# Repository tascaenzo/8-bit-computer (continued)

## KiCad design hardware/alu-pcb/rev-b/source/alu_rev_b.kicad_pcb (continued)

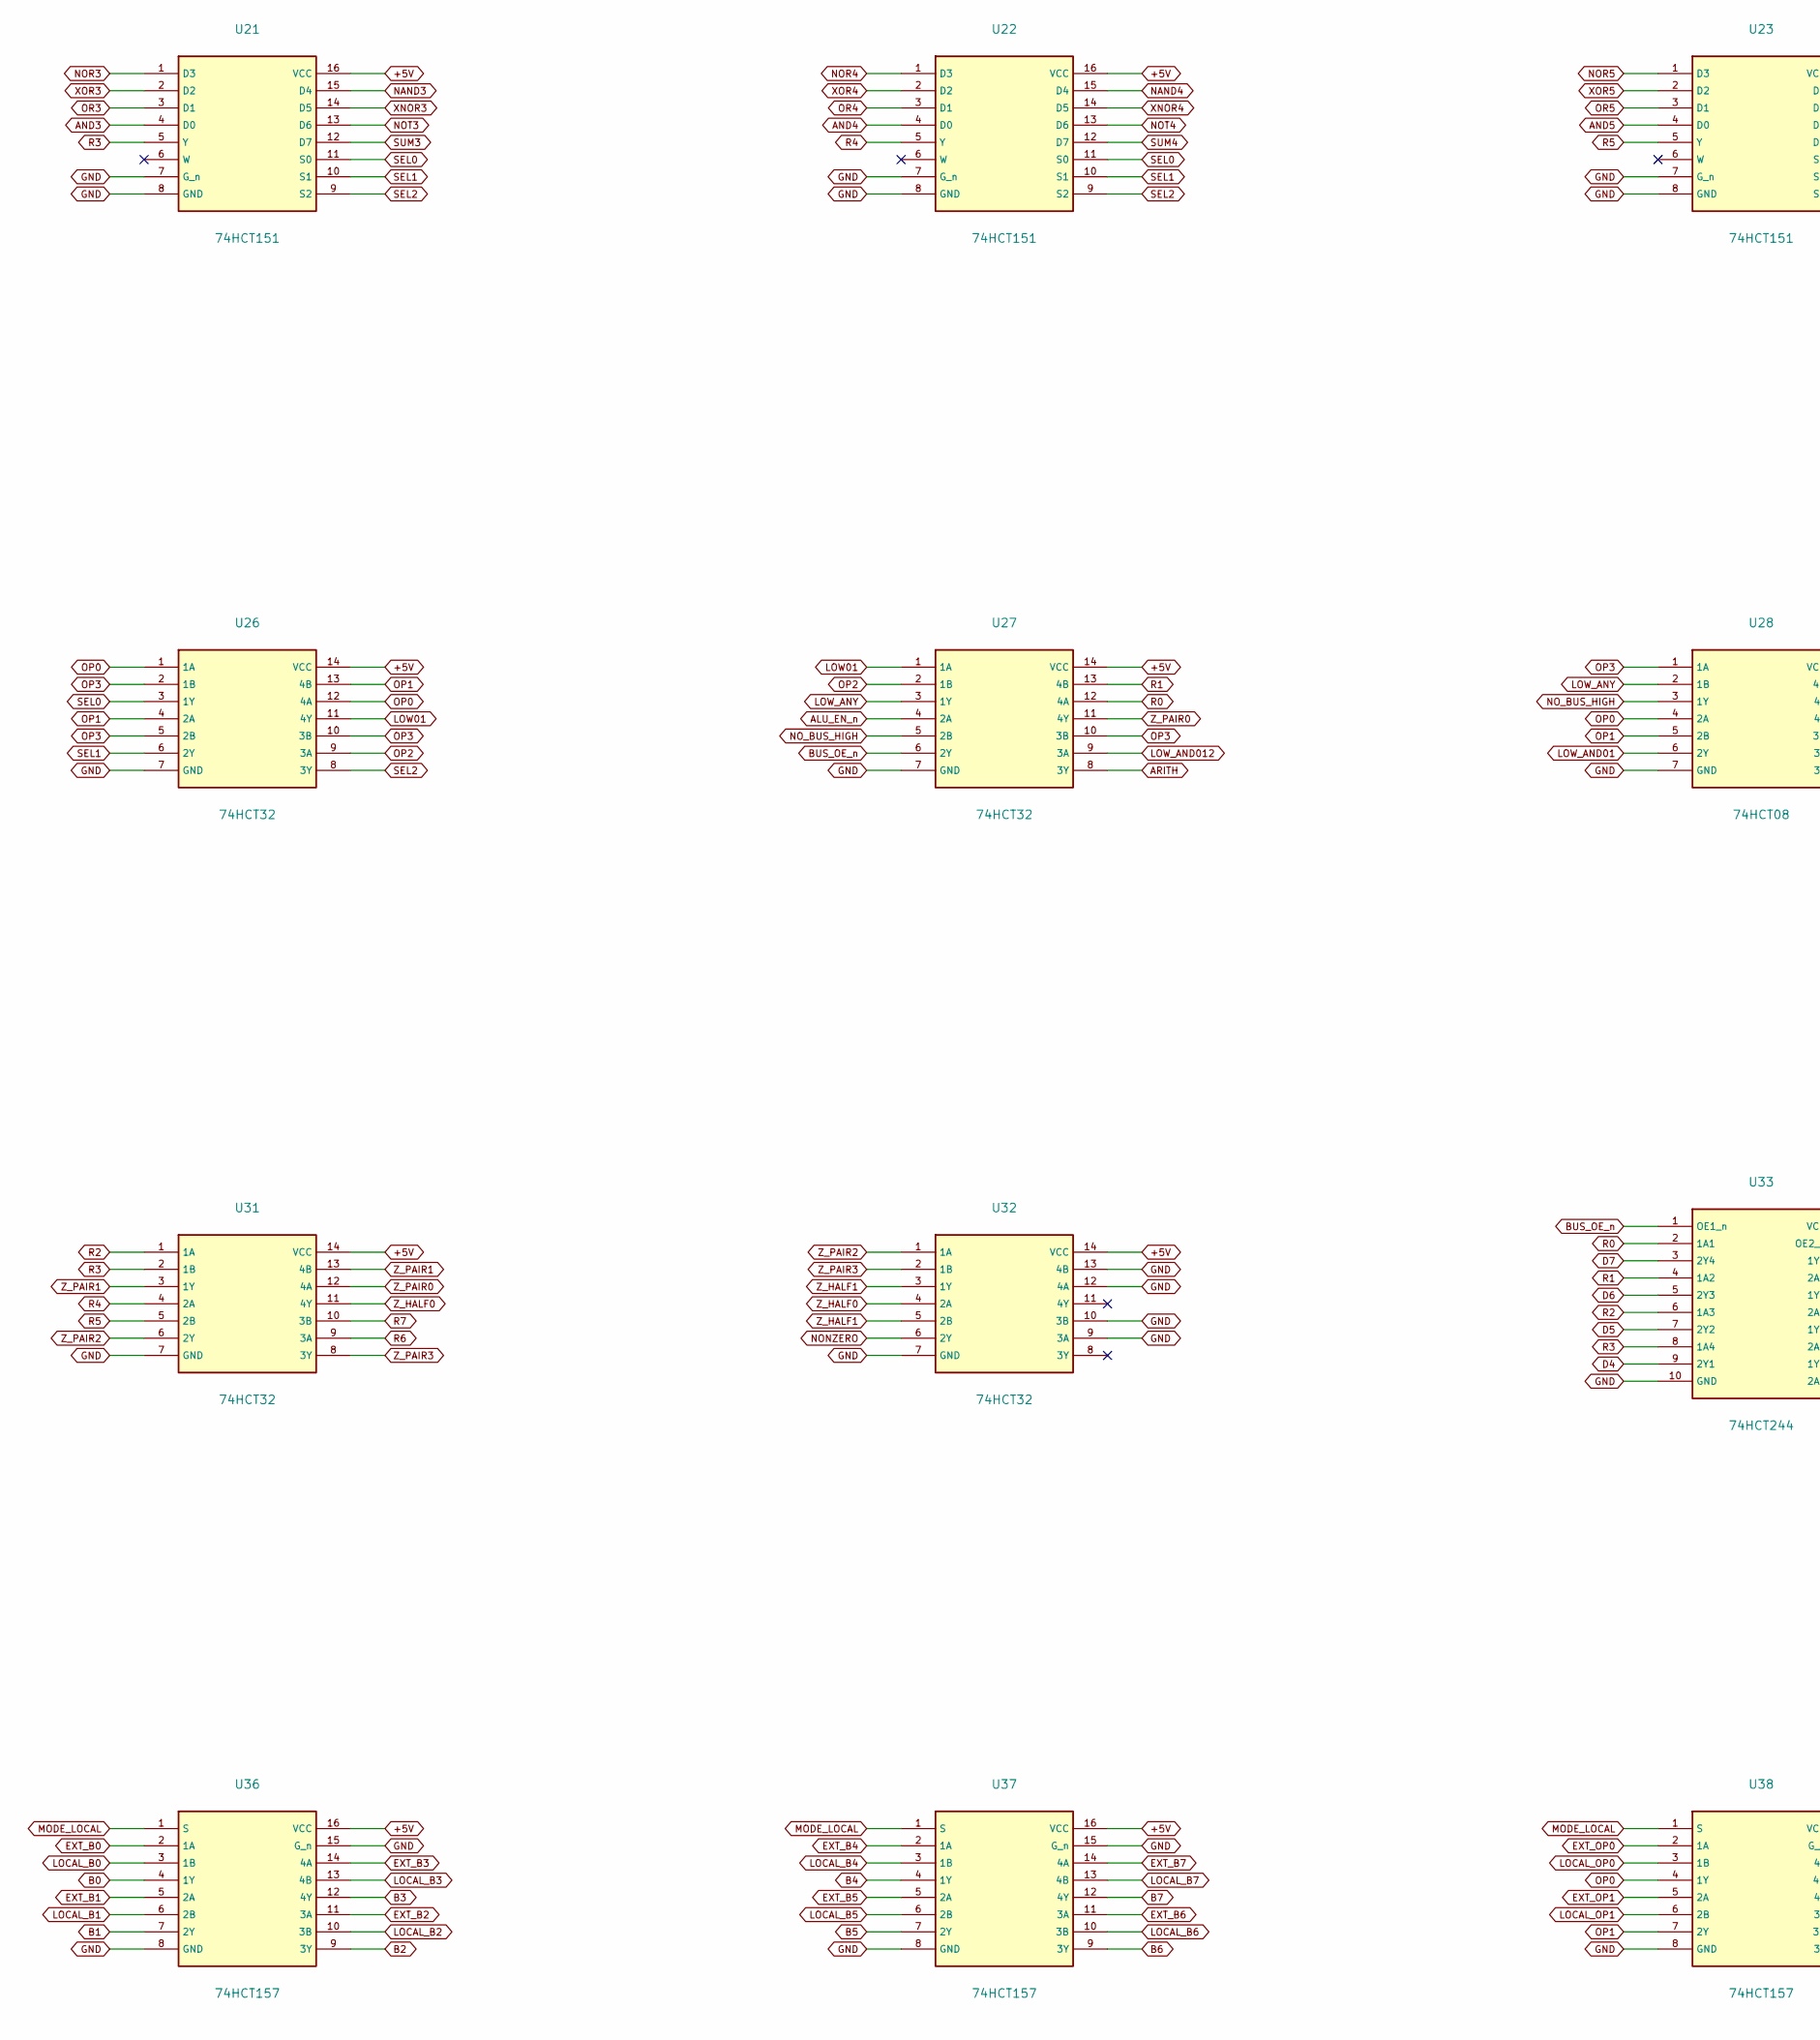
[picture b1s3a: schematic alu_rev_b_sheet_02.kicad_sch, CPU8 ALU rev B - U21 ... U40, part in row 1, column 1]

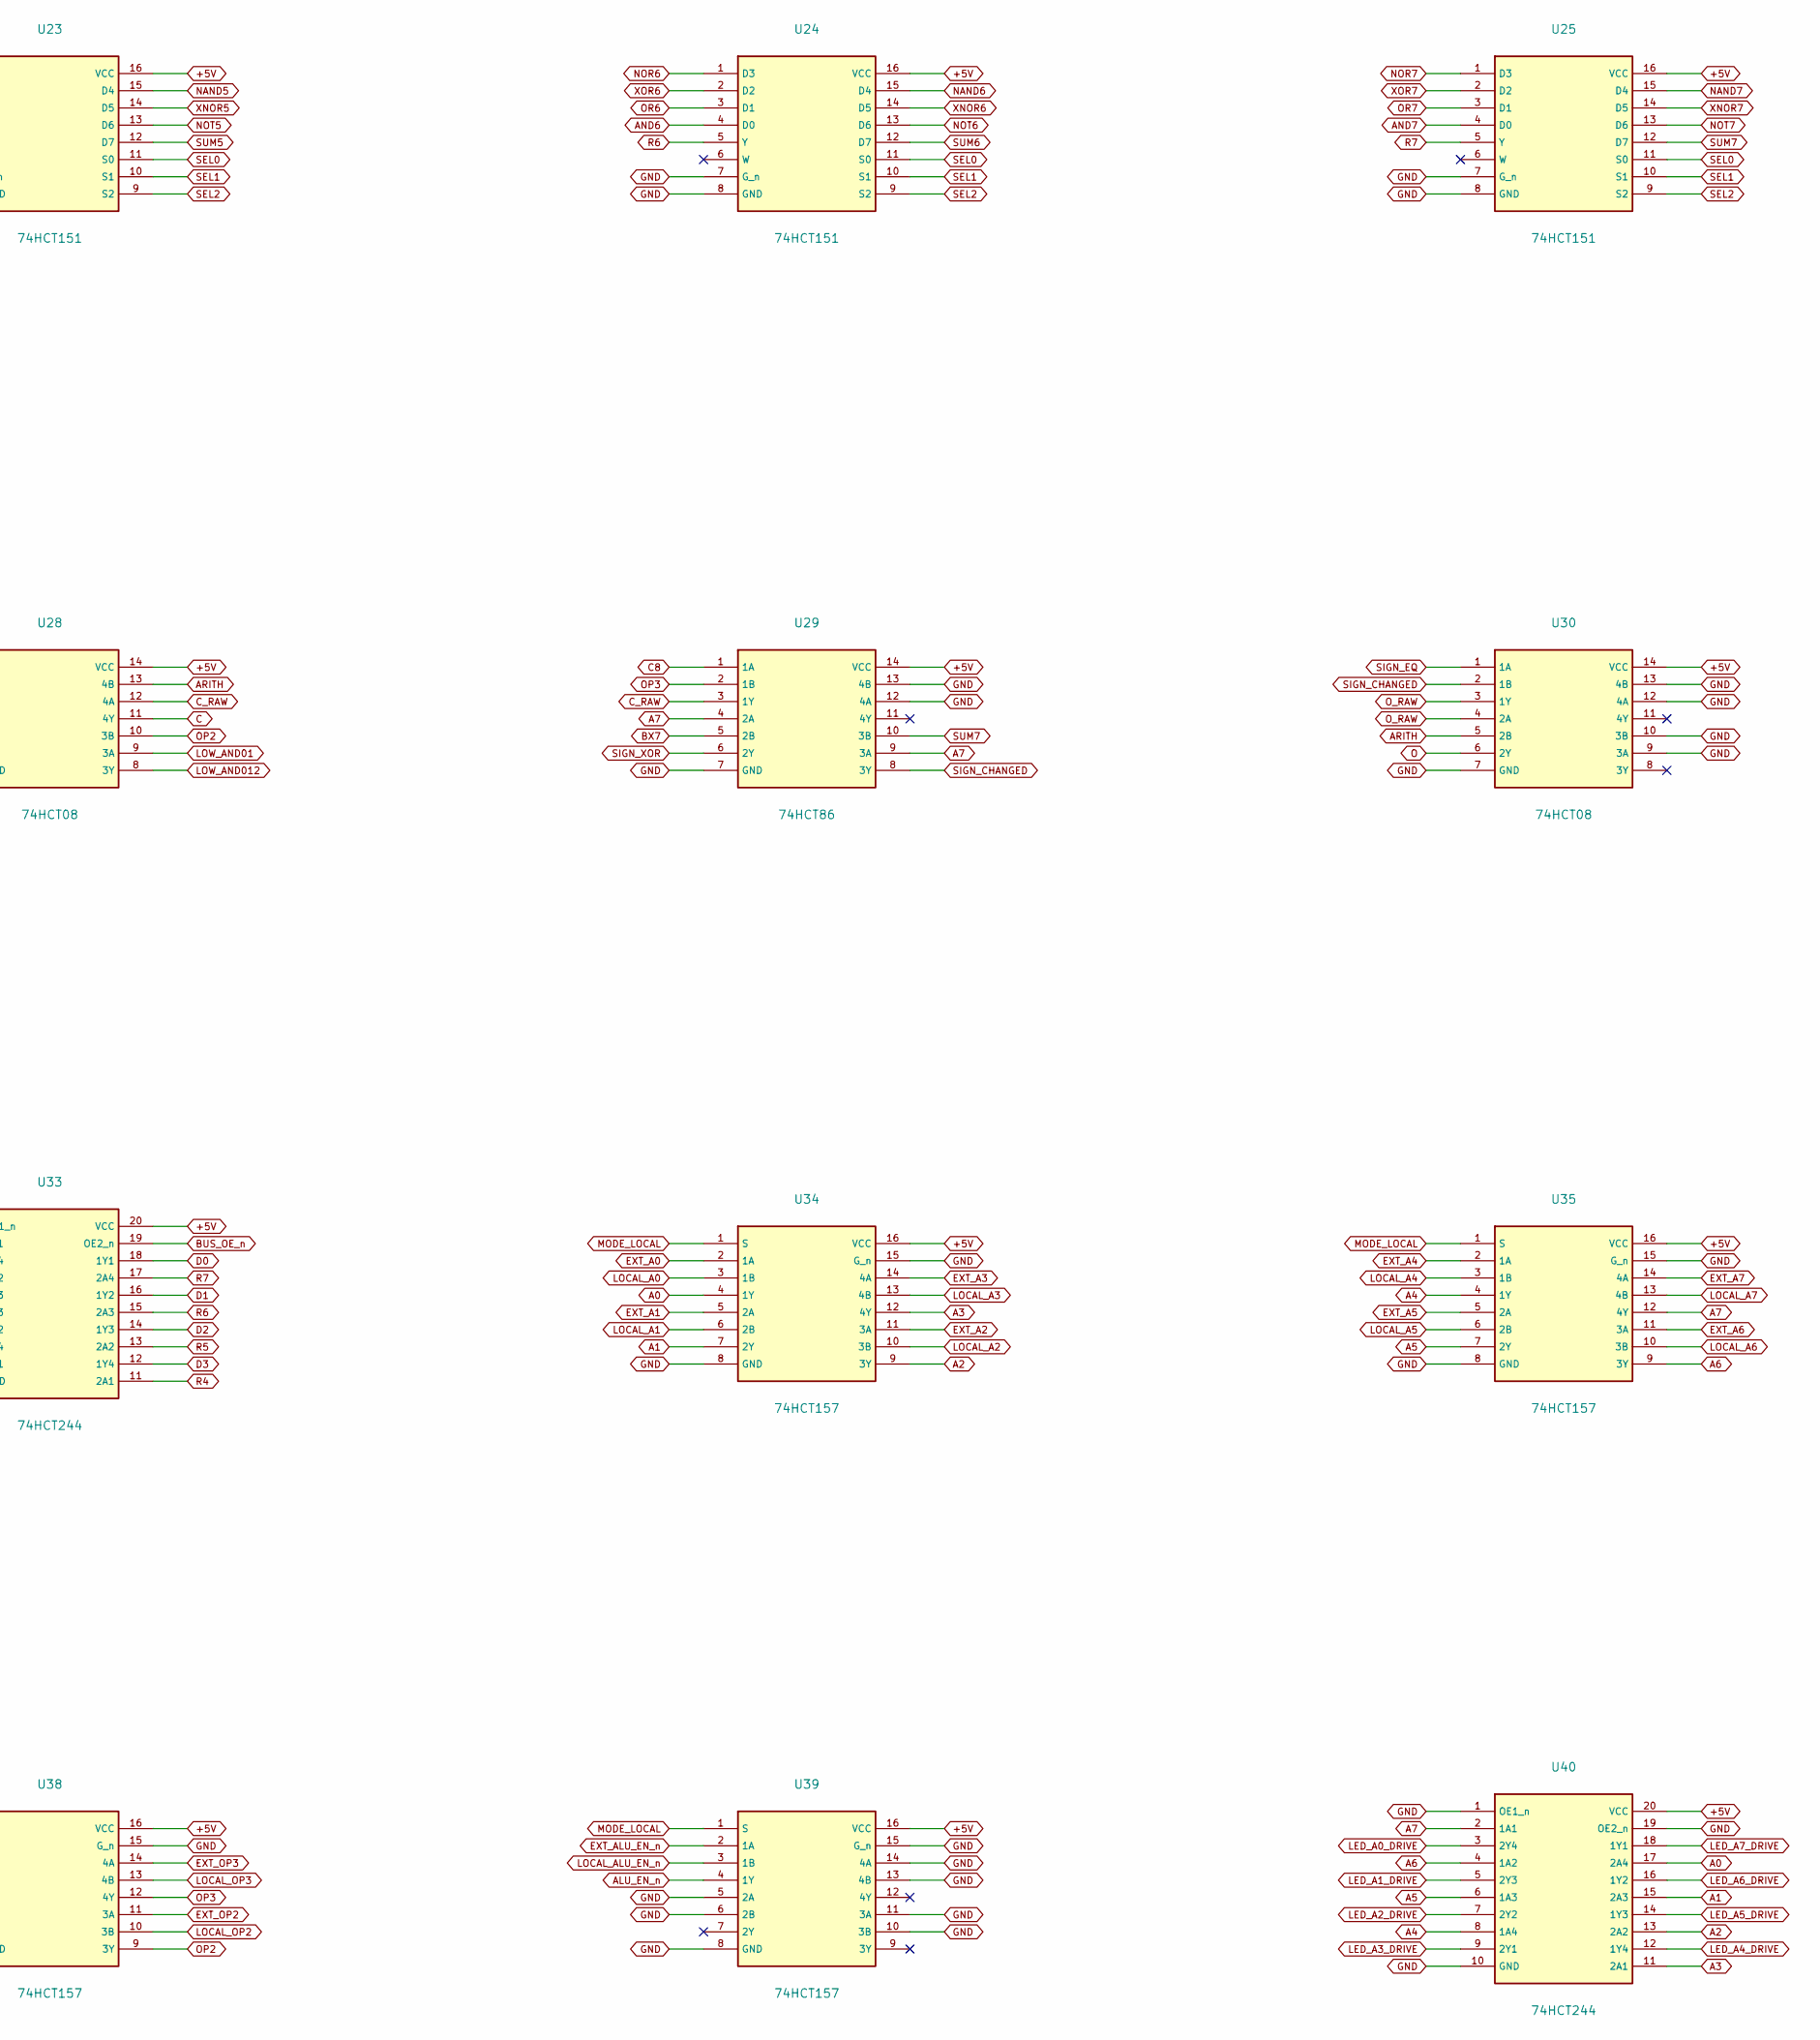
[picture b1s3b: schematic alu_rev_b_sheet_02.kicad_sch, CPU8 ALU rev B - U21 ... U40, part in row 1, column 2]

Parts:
U21, U22, U23, U24, U25: 74HCT151; DIP-16_W7.62mm
U26, U27, U31, U32: 74HCT32; DIP-14_W7.62mm
U28, U30: 74HCT08; DIP-14_W7.62mm
U29: 74HCT86; DIP-14_W7.62mm
U33, U40: 74HCT244; DIP-20_W7.62mm
U34, U35, U36, U37, U38, U39: 74HCT157; DIP-16_W7.62mm

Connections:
+5V: U21.16 (VCC), U22.16 (VCC), U23.16 (VCC), U24.16 (VCC), U25.16 (VCC), U26.14 (VCC), U27.14 (VCC), U28.14 (VCC), U29.14 (VCC), U30.14 (VCC), U31.14 (VCC), U32.14 (VCC), U33.20 (VCC), U34.16 (VCC), U35.16 (VCC), U36.16 (VCC), U37.16 (VCC), U38.16 (VCC), U39.16 (VCC), U40.20 (VCC); also elsewhere on the board
A0: U34.4 (1Y), U40.17 (2A4); also elsewhere on the board
A1: U34.7 (2Y), U40.15 (2A3); also elsewhere on the board
A2: U34.9 (3Y), U40.13 (2A2); also elsewhere on the board
A3: U34.12 (4Y), U40.11 (2A1); also elsewhere on the board
A4: U35.4 (1Y), U40.8 (1A4); also elsewhere on the board
A5: U35.7 (2Y), U40.6 (1A3); also elsewhere on the board
A6: U35.9 (3Y), U40.4 (1A2); also elsewhere on the board
A7: U29.4 (2A), U29.9 (3A), U35.12 (4Y), U40.2 (1A1); also elsewhere on the board
ALU_EN_n: U27.4 (2A), U39.4 (1Y)
AND3: U21.4 (D0); also elsewhere on the board
AND4: U22.4 (D0); also elsewhere on the board
AND5: U23.4 (D0); also elsewhere on the board
AND6: U24.4 (D0); also elsewhere on the board
AND7: U25.4 (D0); also elsewhere on the board
ARITH: U27.8 (3Y), U28.13 (4B), U30.5 (2B)
B0: U36.4 (1Y); also elsewhere on the board
B1: U36.7 (2Y); also elsewhere on the board
B2: U36.9 (3Y); also elsewhere on the board
B3: U36.12 (4Y); also elsewhere on the board
B4: U37.4 (1Y); also elsewhere on the board
B5: U37.7 (2Y); also elsewhere on the board
B6: U37.9 (3Y); also elsewhere on the board
B7: U37.12 (4Y); also elsewhere on the board
BUS_OE_n: U27.6 (2Y), U33.1 (OE1_n), U33.19 (OE2_n)
BX7: U29.5 (2B); also elsewhere on the board
C: U28.11 (4Y); also elsewhere on the board
C8: U29.1 (1A); also elsewhere on the board
C_RAW: U28.12 (4A), U29.3 (1Y)
D0: U33.18 (1Y1); also elsewhere on the board
D1: U33.16 (1Y2); also elsewhere on the board
D2: U33.14 (1Y3); also elsewhere on the board
D3: U33.12 (1Y4); also elsewhere on the board
D4: U33.9 (2Y1); also elsewhere on the board
D5: U33.7 (2Y2); also elsewhere on the board
D6: U33.5 (2Y3); also elsewhere on the board
D7: U33.3 (2Y4); also elsewhere on the board
EXT_A0: U34.2 (1A); also elsewhere on the board
EXT_A1: U34.5 (2A); also elsewhere on the board
EXT_A2: U34.11 (3A); also elsewhere on the board
EXT_A3: U34.14 (4A); also elsewhere on the board
EXT_A4: U35.2 (1A); also elsewhere on the board
EXT_A5: U35.5 (2A); also elsewhere on the board
EXT_A6: U35.11 (3A); also elsewhere on the board
EXT_A7: U35.14 (4A); also elsewhere on the board
EXT_ALU_EN_n: U39.2 (1A); also elsewhere on the board
EXT_B0: U36.2 (1A); also elsewhere on the board
EXT_B1: U36.5 (2A); also elsewhere on the board
EXT_B2: U36.11 (3A); also elsewhere on the board
EXT_B3: U36.14 (4A); also elsewhere on the board
EXT_B4: U37.2 (1A); also elsewhere on the board
EXT_B5: U37.5 (2A); also elsewhere on the board
EXT_B6: U37.11 (3A); also elsewhere on the board
EXT_B7: U37.14 (4A); also elsewhere on the board
EXT_OP0: U38.2 (1A); also elsewhere on the board
EXT_OP1: U38.5 (2A); also elsewhere on the board
EXT_OP2: U38.11 (3A); also elsewhere on the board
EXT_OP3: U38.14 (4A); also elsewhere on the board
GND: U21.7 (G_n), U21.8 (GND), U22.7 (G_n), U22.8 (GND), U23.7 (G_n), U23.8 (GND), U24.7 (G_n), U24.8 (GND), U25.7 (G_n), U25.8 (GND), U26.7 (GND), U27.7 (GND), U28.7 (GND), U29.7 (GND), U29.12 (4A), U29.13 (4B), U30.7 (GND), U30.9 (3A), U30.10 (3B), U30.12 (4A), U30.13 (4B), U31.7 (GND), U32.7 (GND), U32.9 (3A), U32.10 (3B), U32.12 (4A), U32.13 (4B), U33.10 (GND), U34.8 (GND), U34.15 (G_n), U35.8 (GND), U35.15 (G_n), U36.8 (GND), U36.15 (G_n), U37.8 (GND), U37.15 (G_n), U38.8 (GND), U38.15 (G_n), U39.5 (2A), U39.6 (2B), U39.8 (GND), U39.10 (3B), U39.11 (3A), U39.13 (4B), U39.14 (4A), U39.15 (G_n), U40.1 (OE1_n), U40.10 (GND), U40.19 (OE2_n); also elsewhere on the board
LED_A0_DRIVE: U40.3 (2Y4); also elsewhere on the board
LED_A1_DRIVE: U40.5 (2Y3); also elsewhere on the board
LED_A2_DRIVE: U40.7 (2Y2); also elsewhere on the board
LED_A3_DRIVE: U40.9 (2Y1); also elsewhere on the board
LED_A4_DRIVE: U40.12 (1Y4); also elsewhere on the board
LED_A5_DRIVE: U40.14 (1Y3); also elsewhere on the board
LED_A6_DRIVE: U40.16 (1Y2); also elsewhere on the board
LED_A7_DRIVE: U40.18 (1Y1); also elsewhere on the board
LOCAL_A0: U34.3 (1B); also elsewhere on the board
LOCAL_A1: U34.6 (2B); also elsewhere on the board
LOCAL_A2: U34.10 (3B); also elsewhere on the board
LOCAL_A3: U34.13 (4B); also elsewhere on the board
LOCAL_A4: U35.3 (1B); also elsewhere on the board
LOCAL_A5: U35.6 (2B); also elsewhere on the board
LOCAL_A6: U35.10 (3B); also elsewhere on the board
LOCAL_A7: U35.13 (4B); also elsewhere on the board
LOCAL_ALU_EN_n: U39.3 (1B); also elsewhere on the board
LOCAL_B0: U36.3 (1B); also elsewhere on the board
LOCAL_B1: U36.6 (2B); also elsewhere on the board
LOCAL_B2: U36.10 (3B); also elsewhere on the board
LOCAL_B3: U36.13 (4B); also elsewhere on the board
LOCAL_B4: U37.3 (1B); also elsewhere on the board
LOCAL_B5: U37.6 (2B); also elsewhere on the board
LOCAL_B6: U37.10 (3B); also elsewhere on the board
LOCAL_B7: U37.13 (4B); also elsewhere on the board
LOCAL_OP0: U38.3 (1B); also elsewhere on the board
LOCAL_OP1: U38.6 (2B); also elsewhere on the board
LOCAL_OP2: U38.10 (3B); also elsewhere on the board
LOCAL_OP3: U38.13 (4B); also elsewhere on the board
LOW01: U26.11 (4Y), U27.1 (1A)
LOW_AND01: U28.6 (2Y), U28.9 (3A)
LOW_AND012: U27.9 (3A), U28.8 (3Y)
LOW_ANY: U27.3 (1Y), U28.2 (1B)
MODE_LOCAL: U34.1 (S), U35.1 (S), U36.1 (S), U37.1 (S), U38.1 (S), U39.1 (S); also elsewhere on the board
NAND3: U21.15 (D4); also elsewhere on the board
NAND4: U22.15 (D4); also elsewhere on the board
NAND5: U23.15 (D4); also elsewhere on the board
NAND6: U24.15 (D4); also elsewhere on the board
NAND7: U25.15 (D4); also elsewhere on the board
NONZERO: U32.6 (2Y); also elsewhere on the board
NOR3: U21.1 (D3); also elsewhere on the board
NOR4: U22.1 (D3); also elsewhere on the board
NOR5: U23.1 (D3); also elsewhere on the board
NOR6: U24.1 (D3); also elsewhere on the board
NOR7: U25.1 (D3); also elsewhere on the board
NOT3: U21.13 (D6); also elsewhere on the board
NOT4: U22.13 (D6); also elsewhere on the board
NOT5: U23.13 (D6); also elsewhere on the board
NOT6: U24.13 (D6); also elsewhere on the board
NOT7: U25.13 (D6); also elsewhere on the board
NO_BUS_HIGH: U27.5 (2B), U28.3 (1Y)
O: U30.6 (2Y); also elsewhere on the board
OP0: U26.1 (1A), U26.12 (4A), U28.4 (2A), U38.4 (1Y); also elsewhere on the board
OP1: U26.4 (2A), U26.13 (4B), U28.5 (2B), U38.7 (2Y); also elsewhere on the board
OP2: U26.9 (3A), U27.2 (1B), U28.10 (3B), U38.9 (3Y); also elsewhere on the board
OP3: U26.2 (1B), U26.5 (2B), U26.10 (3B), U27.10 (3B), U28.1 (1A), U29.2 (1B), U38.12 (4Y); also elsewhere on the board
OR3: U21.3 (D1); also elsewhere on the board
OR4: U22.3 (D1); also elsewhere on the board
OR5: U23.3 (D1); also elsewhere on the board
OR6: U24.3 (D1); also elsewhere on the board
OR7: U25.3 (D1); also elsewhere on the board
O_RAW: U30.3 (1Y), U30.4 (2A)
R0: U27.12 (4A), U33.2 (1A1); also elsewhere on the board
R1: U27.13 (4B), U33.4 (1A2); also elsewhere on the board
R2: U31.1 (1A), U33.6 (1A3); also elsewhere on the board
R3: U21.5 (Y), U31.2 (1B), U33.8 (1A4); also elsewhere on the board
R4: U22.5 (Y), U31.4 (2A), U33.11 (2A1); also elsewhere on the board
R5: U23.5 (Y), U31.5 (2B), U33.13 (2A2); also elsewhere on the board
R6: U24.5 (Y), U31.9 (3A), U33.15 (2A3); also elsewhere on the board
R7: U25.5 (Y), U31.10 (3B), U33.17 (2A4); also elsewhere on the board
SEL0: U21.11 (S0), U22.11 (S0), U23.11 (S0), U24.11 (S0), U25.11 (S0), U26.3 (1Y); also elsewhere on the board
SEL1: U21.10 (S1), U22.10 (S1), U23.10 (S1), U24.10 (S1), U25.10 (S1), U26.6 (2Y); also elsewhere on the board
SEL2: U21.9 (S2), U22.9 (S2), U23.9 (S2), U24.9 (S2), U25.9 (S2), U26.8 (3Y); also elsewhere on the board
SIGN_CHANGED: U29.8 (3Y), U30.2 (1B)
SIGN_EQ: U30.1 (1A); also elsewhere on the board
SIGN_XOR: U29.6 (2Y); also elsewhere on the board
SUM3: U21.12 (D7); also elsewhere on the board
SUM4: U22.12 (D7); also elsewhere on the board
SUM5: U23.12 (D7); also elsewhere on the board
SUM6: U24.12 (D7); also elsewhere on the board
SUM7: U25.12 (D7), U29.10 (3B); also elsewhere on the board
XNOR3: U21.14 (D5); also elsewhere on the board
XNOR4: U22.14 (D5); also elsewhere on the board
XNOR5: U23.14 (D5); also elsewhere on the board
XNOR6: U24.14 (D5); also elsewhere on the board
XNOR7: U25.14 (D5); also elsewhere on the board
XOR3: U21.2 (D2); also elsewhere on the board
XOR4: U22.2 (D2); also elsewhere on the board
XOR5: U23.2 (D2); also elsewhere on the board
XOR6: U24.2 (D2); also elsewhere on the board
XOR7: U25.2 (D2); also elsewhere on the board
Z_HALF0: U31.11 (4Y), U32.4 (2A)
Z_HALF1: U32.3 (1Y), U32.5 (2B)
Z_PAIR0: U27.11 (4Y), U31.12 (4A)
Z_PAIR1: U31.3 (1Y), U31.13 (4B)
Z_PAIR2: U31.6 (2Y), U32.1 (1A)
Z_PAIR3: U31.8 (3Y), U32.2 (1B)
